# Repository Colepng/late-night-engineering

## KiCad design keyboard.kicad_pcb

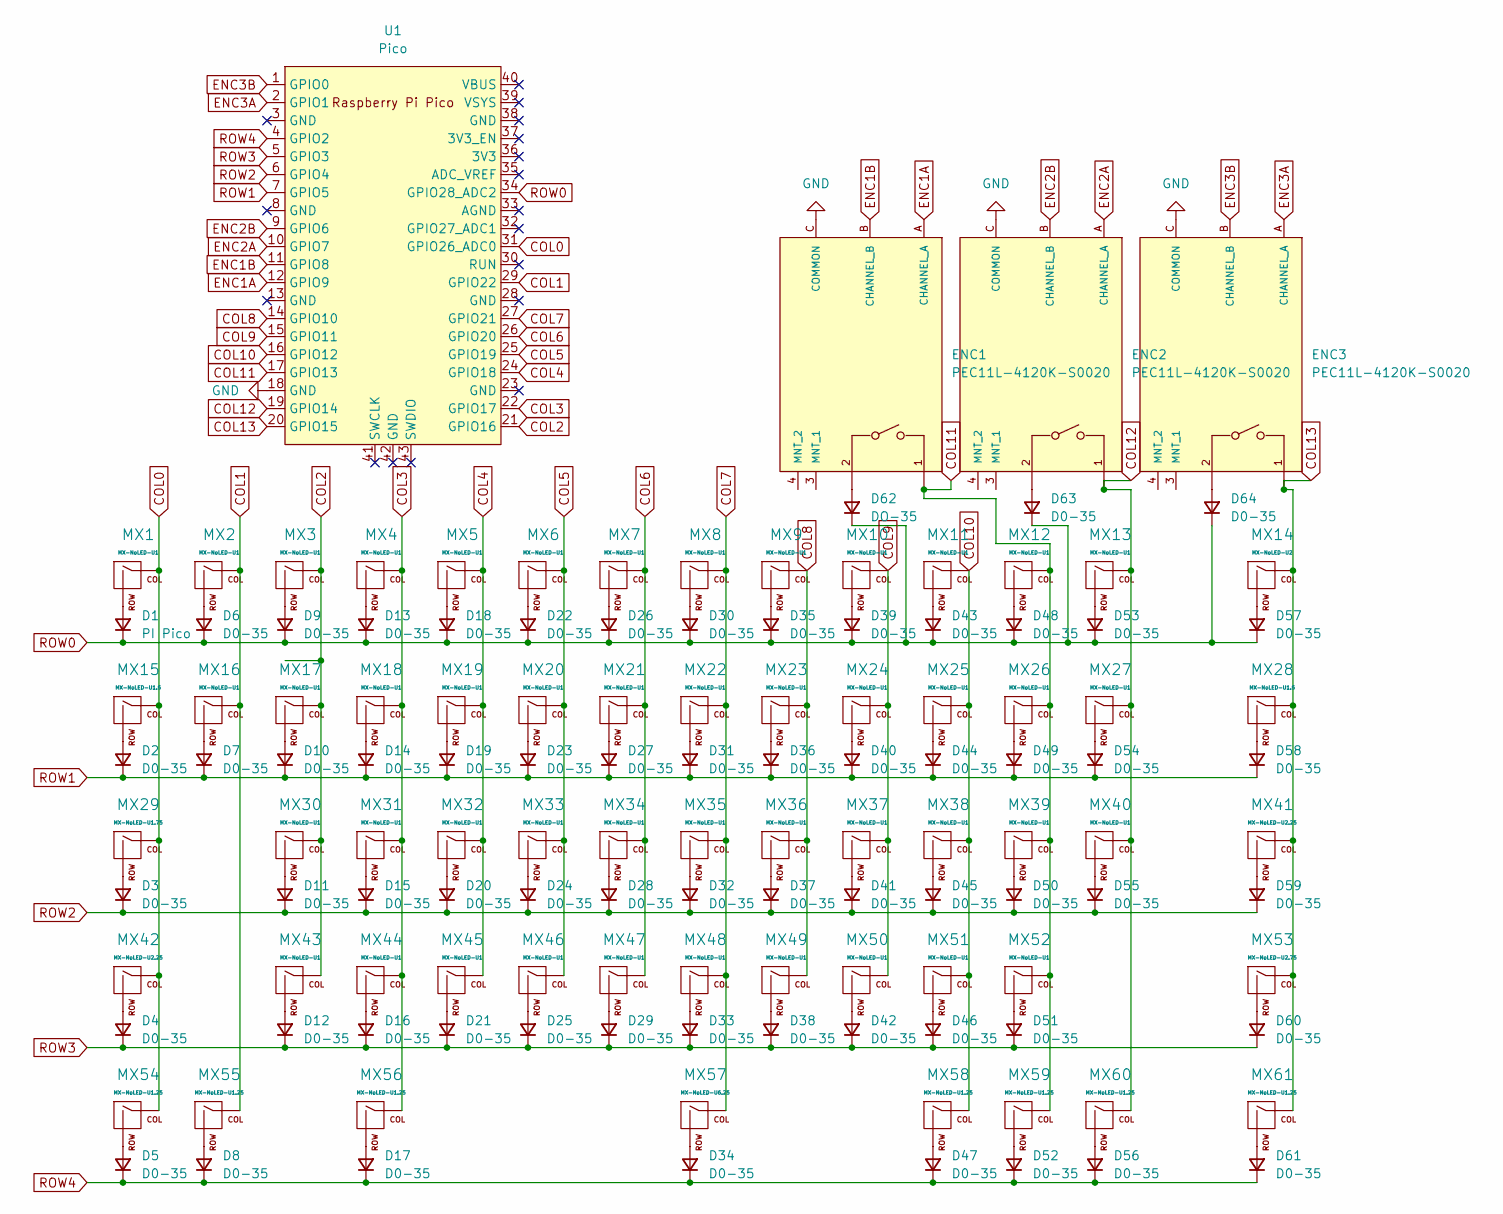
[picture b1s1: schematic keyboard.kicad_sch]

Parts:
D1: PI Pico; ON_Semiconductor-017AG-08_2016-O-MFG
D2, D3, D4, D5, D6, D7, D8, D9, D10, D11, D12, D13, D14, D15, D16, D17, D18, D19, D20, D21, D22, D23, D24, D25, D26, D27, D28, D29, D30, D31, D32, D33, D34, D35, D36, D37, D38, D39, D40, D41, D42, D43, D44, D45, D46, D47, D48, D49, D50, D51, D52, D53, D54, D55, D56, D57, D58, D59, D60, D61, D63, D64: D0-35; ON_Semiconductor-017AG-08_2016-O-MFG
D62: DO-35; ON_Semiconductor-017AG-08_2016-O-MFG
ENC1, ENC2, ENC3: PEC11L-4120K-S0020; Bourns-PEC11L-4120K-S0020-*; current rating 10mA; voltage rating DC 5V; mouser part number 652-PEC11L4120KS0020; digikey description ROTARY ENCODER MECHANICAL 20PPR
MX1, MX2, MX3, MX4, MX5, MX6, MX7, MX8, MX9, MX10, MX11, MX12, MX13, MX16, MX17, MX18, MX19, MX20, MX21, MX22, MX23, MX24, MX25, MX26, MX27, MX30, MX31, MX32, MX33, MX34, MX35, MX36, MX37, MX38, MX39, MX40, MX43, MX44, MX45, MX46, MX47, MX48, MX49, MX50, MX51, MX52: MX-NoLED-U1; MX-1U-NoLED
MX14: MX-NoLED-U2; MX-2U-NoLED
MX15, MX28: MX-NoLED-U1.5; MX-1.5U-NoLED
MX29: MX-NoLED-U1.75; MX-1.75U-NoLED
MX41, MX42: MX-NoLED-U2.25; MX-2.25U-NoLED
MX53: MX-NoLED-U2.75; MX-2.75U-NoLED
MX54, MX55, MX56, MX58, MX59, MX60, MX61: MX-NoLED-U1.25; MX-1.25U-NoLED
MX57: MX-NoLED-U6.25; MX-6.25U-ReversedStabilizers-NoLED
U1: Pico; RPi_Pico_SMD_TH

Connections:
COL0: MX1.1 (COL), MX15.1 (COL), MX29.1 (COL), MX42.1 (COL), MX54.1 (COL), U1.31 (GPIO26_ADC0)
COL1: MX2.1 (COL), MX16.1 (COL), MX55.1 (COL), U1.29 (GPIO22)
COL2: MX3.1 (COL), MX17.1 (COL), MX30.1 (COL), MX43.1 (COL), U1.21 (GPIO16)
COL3: MX4.1 (COL), MX18.1 (COL), MX31.1 (COL), MX44.1 (COL), MX56.1 (COL), U1.22 (GPIO17)
COL4: MX5.1 (COL), MX19.1 (COL), MX32.1 (COL), MX45.1 (COL), U1.24 (GPIO18)
COL5: MX6.1 (COL), MX20.1 (COL), MX33.1 (COL), MX46.1 (COL), U1.25 (GPIO19)
COL6: MX7.1 (COL), MX21.1 (COL), MX34.1 (COL), MX47.1 (COL), U1.26 (GPIO20)
COL7: MX8.1 (COL), MX22.1 (COL), MX35.1 (COL), MX48.1 (COL), MX57.1 (COL), U1.27 (GPIO21)
COL8: MX9.1 (COL), MX23.1 (COL), MX36.1 (COL), MX49.1 (COL), U1.14 (GPIO10)
COL9: MX10.1 (COL), MX24.1 (COL), MX37.1 (COL), MX50.1 (COL), U1.15 (GPIO11)
COL10: MX11.1 (COL), MX25.1 (COL), MX38.1 (COL), MX51.1 (COL), MX58.1 (COL), U1.16 (GPIO12)
COL11: ENC1.1, MX12.1 (COL), MX26.1 (COL), MX39.1 (COL), MX52.1 (COL), MX59.1 (COL), U1.17 (GPIO13); also elsewhere on the board
COL12: ENC2.1, MX13.1 (COL), MX27.1 (COL), MX40.1 (COL), MX60.1 (COL), U1.19 (GPIO14); also elsewhere on the board
COL13: ENC3.1, MX14.1 (COL), MX28.1 (COL), MX41.1 (COL), MX53.1 (COL), MX61.1 (COL), U1.20 (GPIO15); also elsewhere on the board
ENC1A: ENC1.A (CHANNEL_A), U1.12 (GPIO9); also elsewhere on the board
ENC1B: ENC1.B (CHANNEL_B), U1.11 (GPIO8); also elsewhere on the board
ENC2A: ENC2.A (CHANNEL_A), U1.10 (GPIO7); also elsewhere on the board
ENC2B: ENC2.B (CHANNEL_B), U1.9 (GPIO6); also elsewhere on the board
ENC3A: ENC3.A (CHANNEL_A), U1.2 (GPIO1); also elsewhere on the board
ENC3B: ENC3.B (CHANNEL_B), U1.1 (GPIO0); also elsewhere on the board
GND: ENC1.C (COMMON), ENC2.C (COMMON), ENC3.C (COMMON), U1.18 (GND); also elsewhere on the board
unnamed: D1.2 (A), MX1.2 (ROW)
unnamed: D2.2 (A), MX15.2 (ROW)
unnamed: D3.2 (A), MX29.2 (ROW)
unnamed: D4.2 (A), MX42.2 (ROW)
unnamed: D5.2 (A), MX54.2 (ROW)
unnamed: D6.2 (A), MX2.2 (ROW)
unnamed: D7.2 (A), MX16.2 (ROW)
unnamed: D8.2 (A), MX55.2 (ROW)
unnamed: D9.2 (A), MX3.2 (ROW)
unnamed: D10.2 (A), MX17.2 (ROW)
unnamed: D11.2 (A), MX30.2 (ROW)
unnamed: D12.2 (A), MX43.2 (ROW)
unnamed: D13.2 (A), MX4.2 (ROW)
unnamed: D14.2 (A), MX18.2 (ROW)
unnamed: D15.2 (A), MX31.2 (ROW)
unnamed: D16.2 (A), MX44.2 (ROW)
unnamed: D17.2 (A), MX56.2 (ROW)
unnamed: D18.2 (A), MX5.2 (ROW)
unnamed: D19.2 (A), MX19.2 (ROW)
unnamed: D20.2 (A), MX32.2 (ROW)
unnamed: D21.2 (A), MX45.2 (ROW)
unnamed: D22.2 (A), MX6.2 (ROW)
unnamed: D23.2 (A), MX20.2 (ROW)
unnamed: D24.2 (A), MX33.2 (ROW)
unnamed: D25.2 (A), MX46.2 (ROW)
unnamed: D26.2 (A), MX7.2 (ROW)
unnamed: D27.2 (A), MX21.2 (ROW)
unnamed: D28.2 (A), MX34.2 (ROW)
unnamed: D29.2 (A), MX47.2 (ROW)
unnamed: D30.2 (A), MX8.2 (ROW)
unnamed: D31.2 (A), MX22.2 (ROW)
unnamed: D32.2 (A), MX35.2 (ROW)
unnamed: D33.2 (A), MX48.2 (ROW)
unnamed: D34.2 (A), MX57.2 (ROW)
unnamed: D35.2 (A), MX9.2 (ROW)
unnamed: D36.2 (A), MX23.2 (ROW)
unnamed: D37.2 (A), MX36.2 (ROW)
unnamed: D38.2 (A), MX49.2 (ROW)
unnamed: D39.2 (A), MX10.2 (ROW)
unnamed: D40.2 (A), MX24.2 (ROW)
unnamed: D41.2 (A), MX37.2 (ROW)
unnamed: D42.2 (A), MX50.2 (ROW)
unnamed: D43.2 (A), MX11.2 (ROW)
unnamed: D44.2 (A), MX25.2 (ROW)
unnamed: D45.2 (A), MX38.2 (ROW)
unnamed: D46.2 (A), MX51.2 (ROW)
unnamed: D47.2 (A), MX58.2 (ROW)
unnamed: D48.2 (A), MX12.2 (ROW)
unnamed: D49.2 (A), MX26.2 (ROW)
unnamed: D50.2 (A), MX39.2 (ROW)
unnamed: D51.2 (A), MX52.2 (ROW)
unnamed: D52.2 (A), MX59.2 (ROW)
unnamed: D53.2 (A), MX13.2 (ROW)
unnamed: D54.2 (A), MX27.2 (ROW)
unnamed: D55.2 (A), MX40.2 (ROW)
unnamed: D56.2 (A), MX60.2 (ROW)
unnamed: D57.2 (A), MX14.2 (ROW)
unnamed: D58.2 (A), MX28.2 (ROW)
unnamed: D59.2 (A), MX41.2 (ROW)
unnamed: D60.2 (A), MX53.2 (ROW)
unnamed: D61.2 (A), MX61.2 (ROW)
unnamed 82: D62.2 (A), ENC1.2; also elsewhere on the board
unnamed 83: D63.2 (A), ENC2.2; also elsewhere on the board
unnamed 84: D64.2 (A), ENC3.2; also elsewhere on the board
ROW0: D1.1 (K), D6.1 (K), D9.1 (K), D13.1 (K), D18.1 (K), D22.1 (K), D26.1 (K), D30.1 (K), D35.1 (K), D39.1 (K), D43.1 (K), D48.1 (K), D53.1 (K), D57.1 (K), D62.1 (K), D63.1 (K), D64.1 (K), U1.34 (GPIO28_ADC2)
ROW1: D2.1 (K), D7.1 (K), D10.1 (K), D14.1 (K), D19.1 (K), D23.1 (K), D27.1 (K), D31.1 (K), D36.1 (K), D40.1 (K), D44.1 (K), D49.1 (K), D54.1 (K), D58.1 (K), U1.7 (GPIO5)
ROW2: D3.1 (K), D11.1 (K), D15.1 (K), D20.1 (K), D24.1 (K), D28.1 (K), D32.1 (K), D37.1 (K), D41.1 (K), D45.1 (K), D50.1 (K), D55.1 (K), D59.1 (K), U1.6 (GPIO4)
ROW3: D4.1 (K), D12.1 (K), D16.1 (K), D21.1 (K), D25.1 (K), D29.1 (K), D33.1 (K), D38.1 (K), D42.1 (K), D46.1 (K), D51.1 (K), D60.1 (K), U1.5 (GPIO3)
ROW4: D5.1 (K), D8.1 (K), D17.1 (K), D34.1 (K), D47.1 (K), D52.1 (K), D56.1 (K), D61.1 (K), U1.4 (GPIO2)

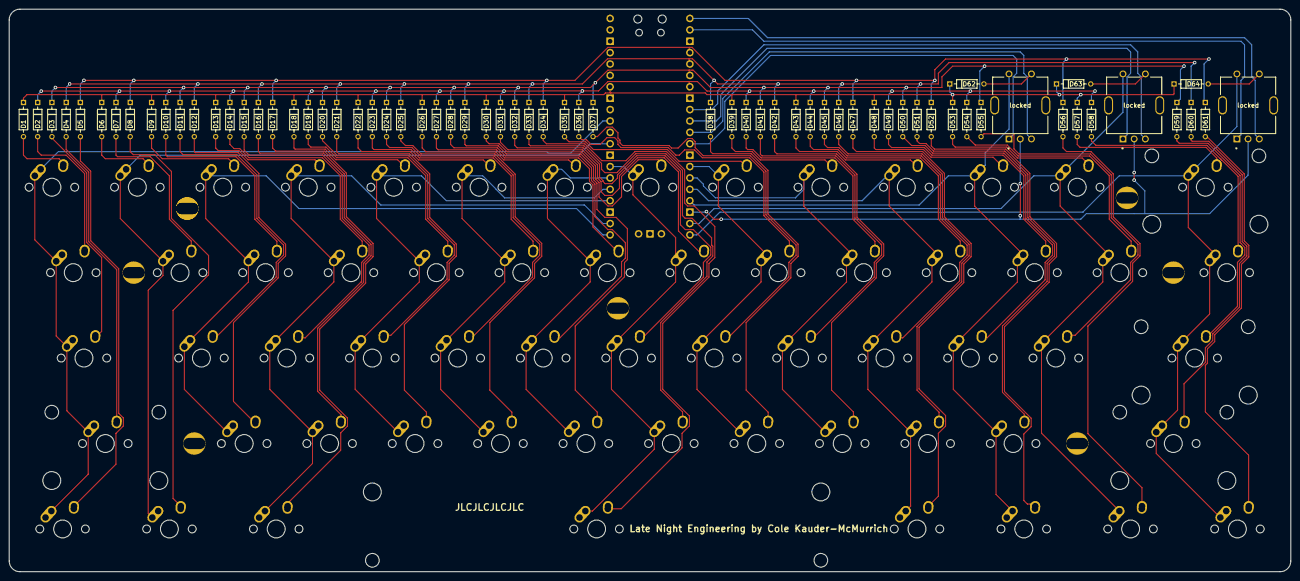
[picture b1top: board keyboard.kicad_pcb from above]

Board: 2 copper layers, 285.8 x 125.4 mm, 129 parts (1 on the bottom side), 90 nets.

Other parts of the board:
locked: locked; Bourns-PEC11L-4120K-S0020-MFG
locked#2, locked#3: locked; Bourns-PEC11L-4120K-S0020-MFG

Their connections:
COL11: locked#2.1; also elsewhere on the board
COL12: locked#3.1; also elsewhere on the board
COL13: locked.1; also elsewhere on the board
ENC1A: locked#2.A (CHANNEL_A); also elsewhere on the board
ENC1B: locked#2.B (CHANNEL_B); also elsewhere on the board
ENC2A: locked#3.A (CHANNEL_A); also elsewhere on the board
ENC2B: locked#3.B (CHANNEL_B); also elsewhere on the board
ENC3A: locked.A (CHANNEL_A); also elsewhere on the board
ENC3B: locked.B (CHANNEL_B); also elsewhere on the board
GND: locked.C (COMMON), locked#2.C (COMMON), locked#3.C (COMMON); also elsewhere on the board
unnamed 82: locked#2.2; also elsewhere on the board
unnamed 83: locked#3.2; also elsewhere on the board
unnamed 84: locked.2; also elsewhere on the board

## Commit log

2023-05-19 Init keyboard
2023-05-19 Done schematic
2023-05-19 Matrix placed
2023-05-22 Got everything placed
2023-05-22 forgot to save
2023-05-24 Routed diodes to switches
2023-05-25 Tracing mostly done just do DRC
2023-05-26 Should be completely done
2023-05-26 With brakeouts
2023-05-26 Remove brakouts
2023-06-01 Add gerbers
2023-09-15 Uploaded photo of keyboard
2023-10-07 Added a resources list
